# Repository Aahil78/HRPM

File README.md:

# HRPM - A High Speed PID Based Line Follower
A very fast Line Following Robot with a cusom IR Array and control PCB, uses PID Based algorithim.

## Features:
  - High Speed for fast track completion
  - Custom 20 Sensor IR Array Module for precision
  - Integrated MCU, Motor Driver, and LiPo System (Charger Seperate) For good control and OTA PID Tuning -- COMING SOON
  - Custom 3D Printed Chassis for modularity. -- COMING SOON
  - More to come soon!

## Why I made this:

I made this because I go to comps often and many times I lose, I've noticed that many bots aren't fast so I decided; what if I make a high speed LFR, that'll help me win comps and get some prizes and network around with people.

## Images:

### IR Array

### IR Array Breakout (For testing & Prototyping)

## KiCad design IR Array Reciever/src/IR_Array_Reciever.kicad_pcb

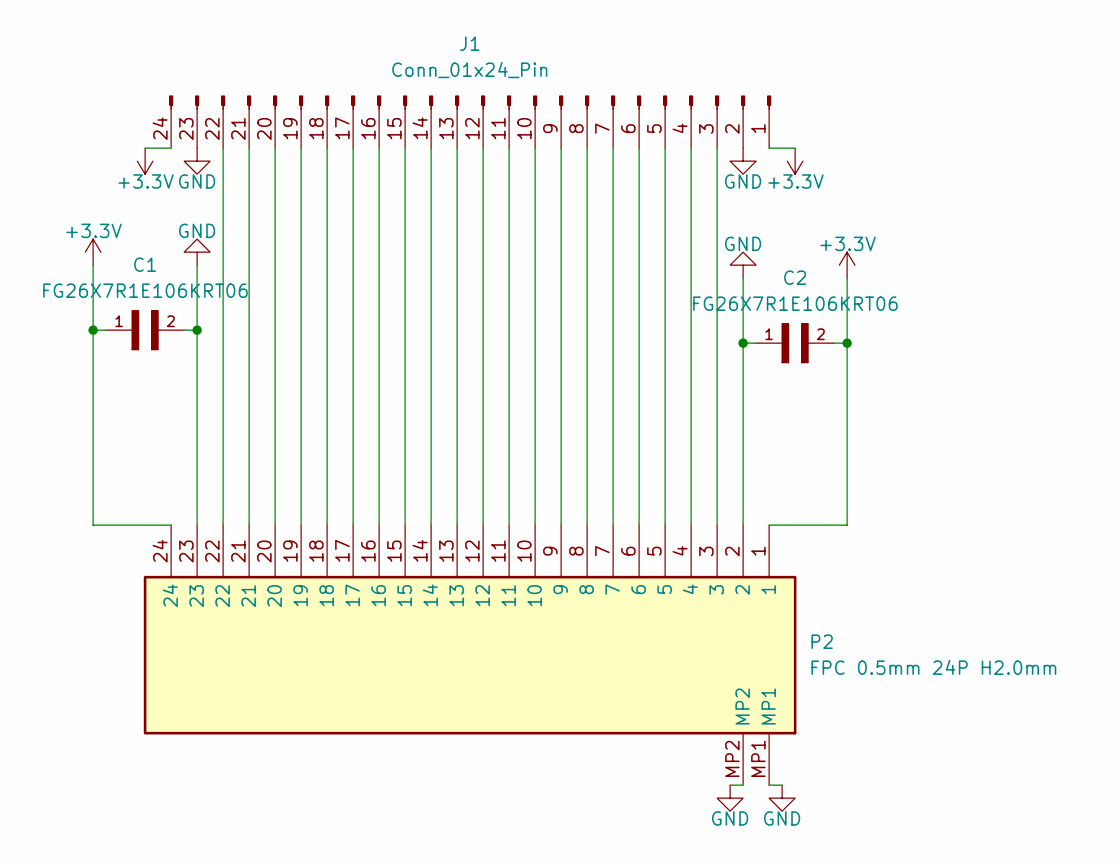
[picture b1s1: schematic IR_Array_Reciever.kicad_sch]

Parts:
C1, C2: FG26X7R1E106KRT06; CAPRB500W50L550T350H600; PARTREV 20200310
J1: Conn_01x24_Pin; PinHeader_1x24_P2.54mm_Vertical
P2: FPC 0.5mm 24P H2.0mm; AFC07S24ECC00; Manufacturer_Part_Number AFC07-S24ECC-00; LCSC C11092

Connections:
+3.3V: C1.1, C2.2, J1.1, J1.24, P2.1, P2.24
GND: C1.2, C2.1, J1.2, J1.23, P2.2, P2.23, P2.MP1, P2.MP2
unnamed: J1.3, P2.3
unnamed: J1.4, P2.4
unnamed: J1.5, P2.5
unnamed: J1.6, P2.6
unnamed: J1.7, P2.7
unnamed: J1.8, P2.8
unnamed: J1.9, P2.9
unnamed: J1.10, P2.10
unnamed: J1.11, P2.11
unnamed: J1.12, P2.12
unnamed: J1.13, P2.13
unnamed: J1.14, P2.14
unnamed: J1.15, P2.15
unnamed: J1.16, P2.16
unnamed: J1.17, P2.17
unnamed: J1.18, P2.18
unnamed: J1.19, P2.19
unnamed: J1.20, P2.20
unnamed: J1.21, P2.21
unnamed: J1.22, P2.22

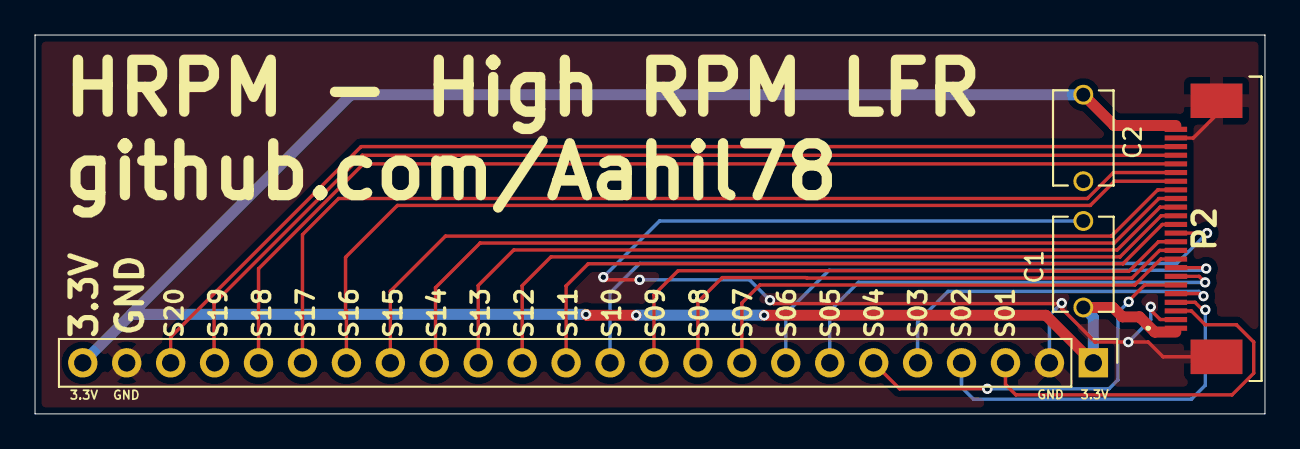
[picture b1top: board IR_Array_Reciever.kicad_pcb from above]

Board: 2 copper layers, 71.1 x 21.9 mm, 4 parts (0 on the bottom side), 22 nets.

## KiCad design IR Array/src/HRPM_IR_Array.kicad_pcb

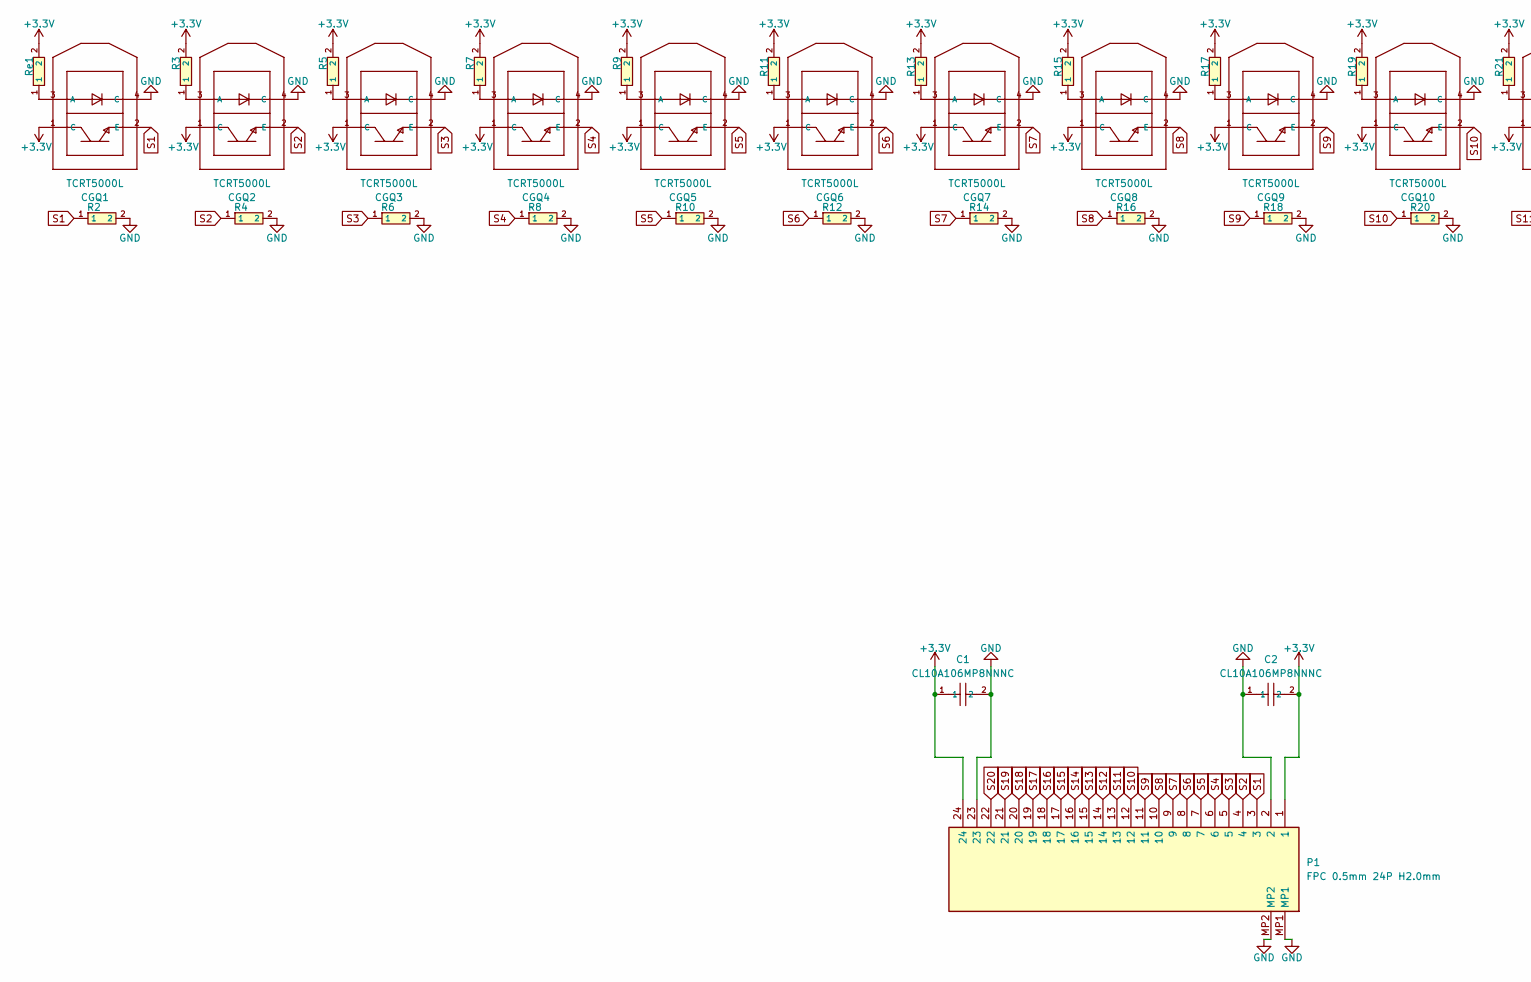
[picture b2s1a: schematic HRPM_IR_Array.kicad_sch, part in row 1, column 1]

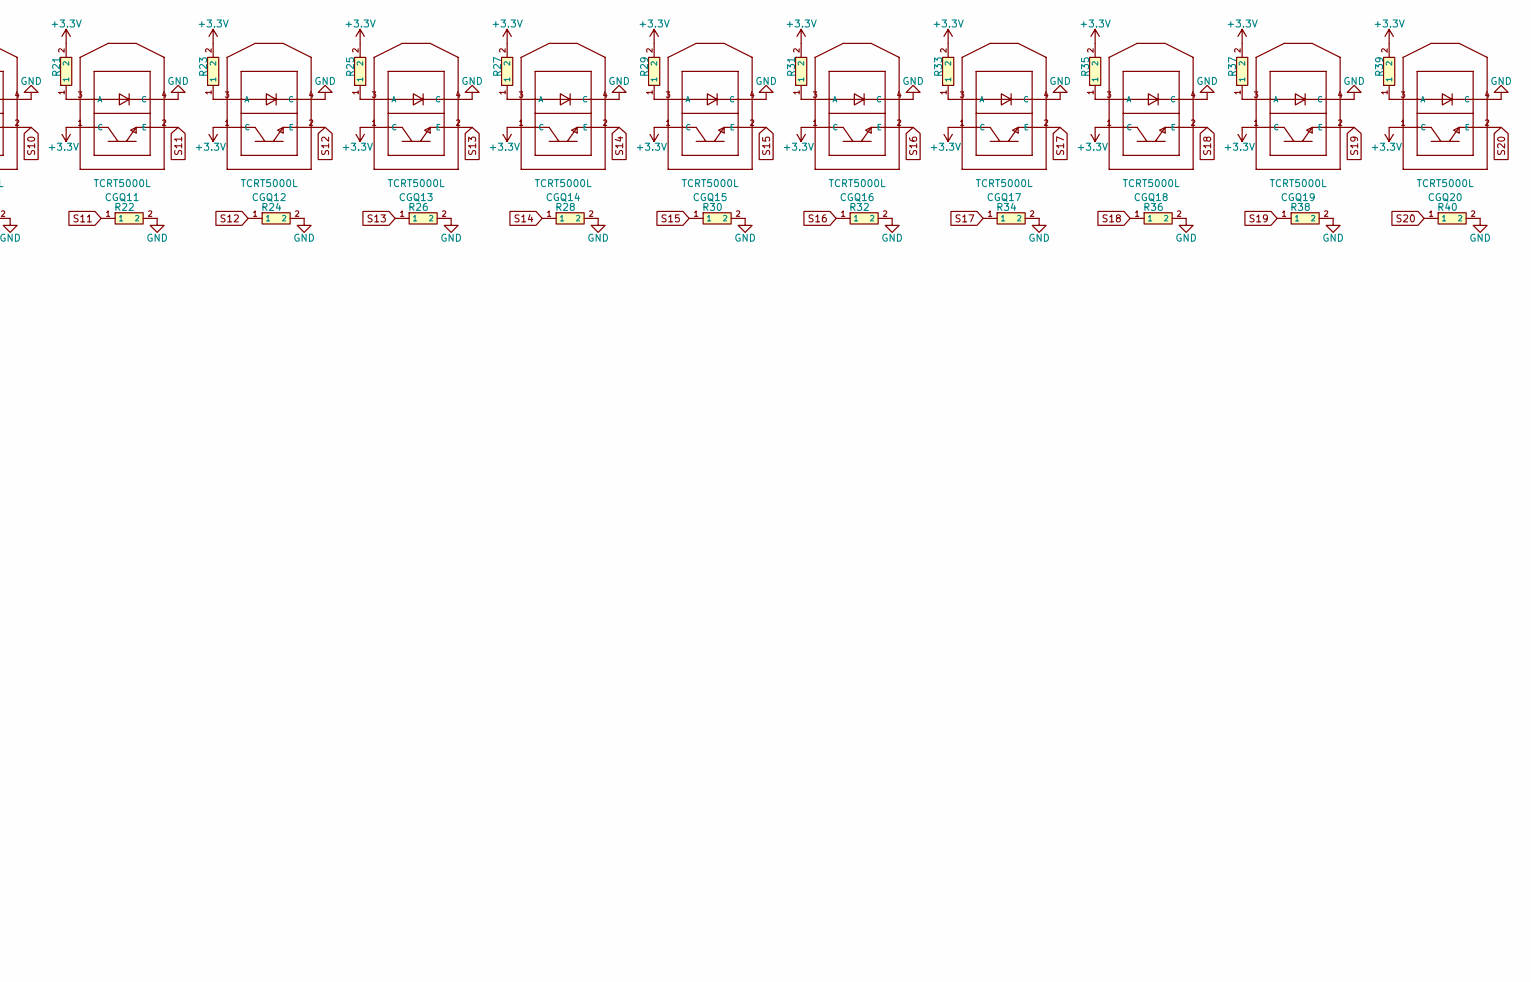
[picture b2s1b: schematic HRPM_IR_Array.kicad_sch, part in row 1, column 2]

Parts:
C1, C2: CL10A106MP8NNNC; C85713_C0603; LCSC C85713
CGQ1, CGQ2, CGQ3, CGQ4, CGQ5, CGQ6, CGQ7, CGQ8, CGQ9, CGQ10, CGQ11, CGQ12, CGQ13, CGQ14, CGQ15, CGQ16, CGQ17, CGQ18, CGQ19, CGQ20: TCRT5000L; XDCR_TCRT5000L; LCSC C24085
P1: FPC 0.5mm 24P H2.0mm; AFC07S24ECC00; Manufacturer_Part_Number AFC07-S24ECC-00; LCSC C11092
R2, R4, R6, R8, R10, R12, R14, R16, R18, R20, R22, R24, R26, R28, R30, R32, R34, R36, R38, R40: RC0603FR-0710KL; C98220_R0603; LCSC C98220
R3, R5, R7, R9, R11, R13, R15, R17, R19, R21, R23, R25, R27, R29, R31, R33, R35, R37, R39: RC0603FR-07220RL; BatteryHolder_Keystone_3002_1x2032; LCSC C107696
Re1: RC0603FR-07220RL; C107696_R0603; LCSC C107696

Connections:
+3.3V: C1.1, C2.2, CGQ1.1 (C), CGQ2.1 (C), CGQ3.1 (C), CGQ4.1 (C), CGQ5.1 (C), CGQ6.1 (C), CGQ7.1 (C), CGQ8.1 (C), CGQ9.1 (C), CGQ10.1 (C), CGQ11.1 (C), CGQ12.1 (C), CGQ13.1 (C), CGQ14.1 (C), CGQ15.1 (C), CGQ16.1 (C), CGQ17.1 (C), CGQ18.1 (C), CGQ19.1 (C), CGQ20.1 (C), P1.1, P1.24, R3.2, R5.2, R7.2, R9.2, R11.2, R13.2, R15.2, R17.2, R19.2, R21.2, R23.2, R25.2, R27.2, R29.2, R31.2, R33.2, R35.2, R37.2, R39.2, Re1.2; also elsewhere on the board
GND: C1.2, C2.1, CGQ1.4 (C), CGQ2.4 (C), CGQ3.4 (C), CGQ4.4 (C), CGQ5.4 (C), CGQ6.4 (C), CGQ7.4 (C), CGQ8.4 (C), CGQ9.4 (C), CGQ10.4 (C), CGQ11.4 (C), CGQ12.4 (C), CGQ13.4 (C), CGQ14.4 (C), CGQ15.4 (C), CGQ16.4 (C), CGQ17.4 (C), CGQ18.4 (C), CGQ19.4 (C), CGQ20.4 (C), P1.2, P1.23, P1.MP1, P1.MP2, R2.2, R4.2, R6.2, R8.2, R10.2, R12.2, R14.2, R16.2, R18.2, R20.2, R22.2, R24.2, R26.2, R28.2, R30.2, R32.2, R34.2, R36.2, R38.2, R40.2
unnamed 2: CGQ1.3 (A), Re1.1; also elsewhere on the board
unnamed: CGQ2.3 (A), R3.1
unnamed: CGQ3.3 (A), R5.1
unnamed: CGQ4.3 (A), R7.1
unnamed: CGQ5.3 (A), R9.1
unnamed: CGQ6.3 (A), R11.1
unnamed: CGQ7.3 (A), R13.1
unnamed: CGQ8.3 (A), R15.1
unnamed: CGQ9.3 (A), R17.1
unnamed: CGQ10.3 (A), R19.1
unnamed: CGQ11.3 (A), R21.1
unnamed: CGQ12.3 (A), R23.1
unnamed: CGQ13.3 (A), R25.1
unnamed: CGQ14.3 (A), R27.1
unnamed: CGQ15.3 (A), R29.1
unnamed: CGQ16.3 (A), R31.1
unnamed: CGQ17.3 (A), R33.1
unnamed: CGQ18.3 (A), R35.1
unnamed: CGQ19.3 (A), R37.1
unnamed: CGQ20.3 (A), R39.1
S1: CGQ1.2 (E), P1.3, R2.1
S2: CGQ2.2 (E), P1.4, R4.1
S3: CGQ3.2 (E), P1.5, R6.1
S4: CGQ4.2 (E), P1.6, R8.1
S5: CGQ5.2 (E), P1.7, R10.1
S6: CGQ6.2 (E), P1.8, R12.1
S7: CGQ7.2 (E), P1.9, R14.1
S8: CGQ8.2 (E), P1.10, R16.1
S9: CGQ9.2 (E), P1.11, R18.1
S10: CGQ10.2 (E), P1.12, R20.1
S11: CGQ11.2 (E), P1.13, R22.1
S12: CGQ12.2 (E), P1.14, R24.1
S13: CGQ13.2 (E), P1.15, R26.1
S14: CGQ14.2 (E), P1.16, R28.1
S15: CGQ15.2 (E), P1.17, R30.1
S16: CGQ16.2 (E), P1.18, R32.1
S17: CGQ17.2 (E), P1.19, R34.1
S18: CGQ18.2 (E), P1.20, R36.1
S19: CGQ19.2 (E), P1.21, R38.1
S20: CGQ20.2 (E), P1.22, R40.1

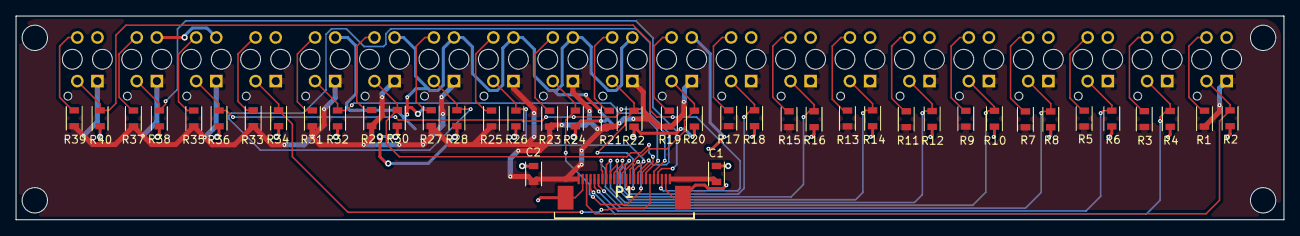
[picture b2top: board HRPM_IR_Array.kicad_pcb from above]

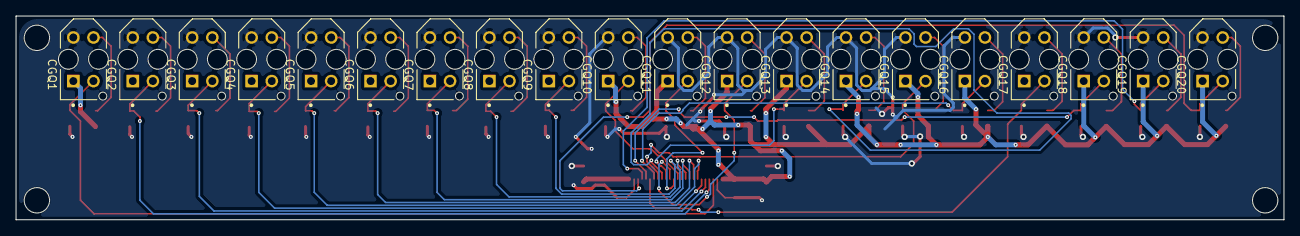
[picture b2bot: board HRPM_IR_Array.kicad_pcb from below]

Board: 2 copper layers, 160.0 x 25.7 mm, 63 parts (20 on the bottom side), 42 nets.

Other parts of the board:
R1: RC0603FR-07220RL; C107696_R0603

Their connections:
+3.3V: R1.2; also elsewhere on the board
unnamed 2: R1.1; also elsewhere on the board

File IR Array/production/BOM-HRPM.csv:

Comment,Designator,Footprint,LCSC,Quantity
CL10A106MP8NNNC,"C1,C2",C85713_C0603,C85713,2
FPC 0.5mm 24P H2.0mm,P1,AFC07S24ECC00,C11092,1
RC0603FR-0710KL,"R10,R12,R14,R16,R18,R2,R20,R22,R24,R26,R28,R30,R32,R34,R36,R38,R4,R40,R6,R8",C98220_R0603,C98220,20
RC0603FR-07220RL,"R1,R11,R13,R15,R17,R19,R21,R23,R25,R27,R29,R3,R31,R33,R35,R37,R39,R5,R7,R9",C107696_R0603,C107696,20
TCRT5000L,"CGQ1,CGQ10,CGQ11,CGQ12,CGQ13,CGQ14,CGQ15,CGQ16,CGQ17,CGQ18,CGQ19,CGQ2,CGQ20,CGQ3,CGQ4,CGQ5,CGQ6,CGQ7,CGQ8,CGQ9",XDCR_TCRT5000L,C24085,20

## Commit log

2026-05-09 Make README
2026-05-10 Add IR Array Files
2026-05-10 Add IR Array breakout files.
